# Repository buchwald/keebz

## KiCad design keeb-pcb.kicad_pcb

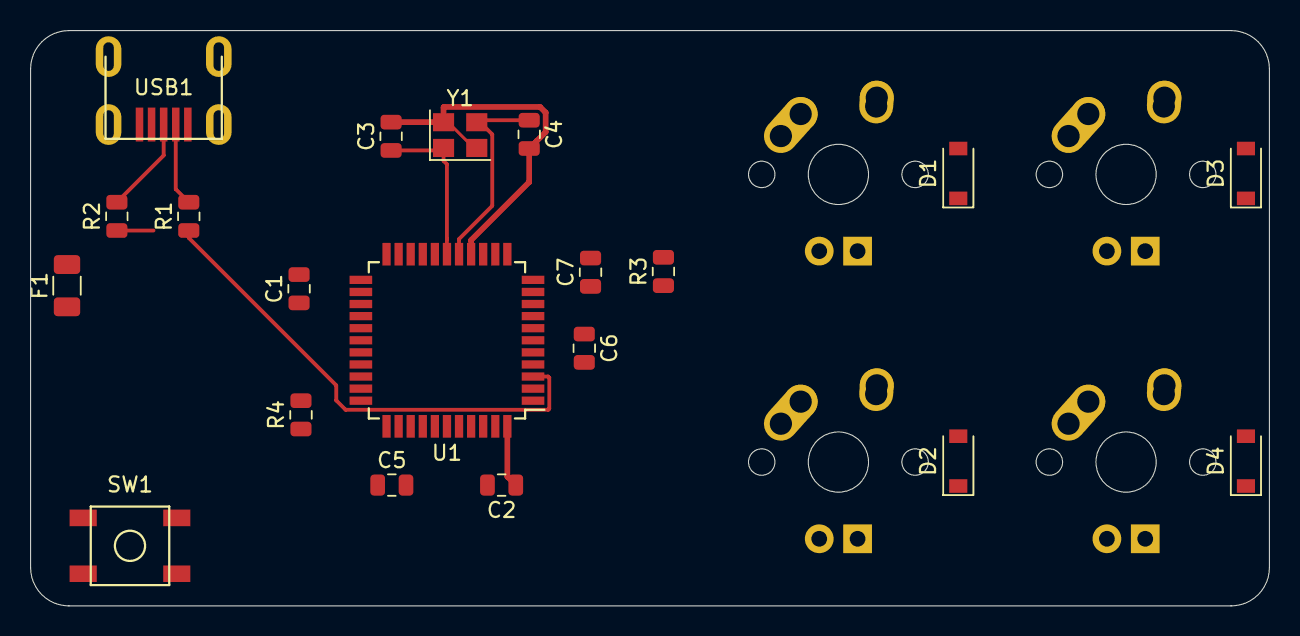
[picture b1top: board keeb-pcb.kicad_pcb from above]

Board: 2 copper layers, 82.0 x 38.1 mm, 24 parts (0 on the bottom side), 20 nets.

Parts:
C1, C2, C5, C7: 0.1uF; C_0805_2012Metric
C3, C4: 22pF; C_0805_2012Metric
C6: 1uF; C_0805_2012Metric
D1, D2, D3, D4: D_Small; D_SOD-123
F1: 500mA; Fuse_1206_3216Metric
MX1, MX2, MX3, MX4: MX-NoLED; MX-1U
R1, R2: 22; R_0805_2012Metric
R3, R4: 10k; R_0805_2012Metric
SW1: SW_Push; SKQG-1155865
U1: ATmega32U4-AU; TQFP-44_10x10mm_P0.8mm
USB1: Molex-0548190589
Y1: 16MHz; Crystal_SMD_3225-4Pin_3.2x2.5mm

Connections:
+5V: C1.1, C2.1, C5.1, C7.1, F1.1, R3.1, U1.2, U1.7, U1.14, U1.24, U1.34, U1.44
COL0: MX1.1, MX2.1
COL1: MX3.1, MX4.1
D+: R2.2, USB1.3
D-: R1.2, USB1.4
GND: C1.2, C2.2, C3.2, C4.2, C5.2, C6.2, C7.2, SW1.1, U1.5, U1.15, U1.23, U1.35, U1.43, USB1.1, Y1.2, Y1.4
unnamed: C3.1, U1.17, Y1.1
unnamed: C4.1, U1.16, Y1.3
unnamed: C6.1, U1.6
unnamed: D1.2, MX1.2
unnamed: D2.2, MX2.2
unnamed: D3.2, MX3.2
unnamed: D4.2, MX4.2
unnamed: R1.1, U1.3
unnamed: R2.1, U1.4
unnamed: R3.2, SW1.2, U1.13
unnamed: R4.2, U1.33
ROW0: D1.1, D3.1
ROW1: D2.1, D4.1
VCC: F1.2, USB1.5

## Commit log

2020-05-07 kicad project init
    commit of initial KiCad project files
2020-05-07 Add submodules
2020-05-07 adding kicad libraries
2020-05-10 MCU schematic
    PCB Guide Part 3
2020-05-10 USB and Matrix Schematic
    Added USB connector and Matrix Switches. PCB Guide Part 4
2020-05-10 Footprints
    Assigned Footprints to Schematic - PCB Guide Part 4
2020-05-10 routing
